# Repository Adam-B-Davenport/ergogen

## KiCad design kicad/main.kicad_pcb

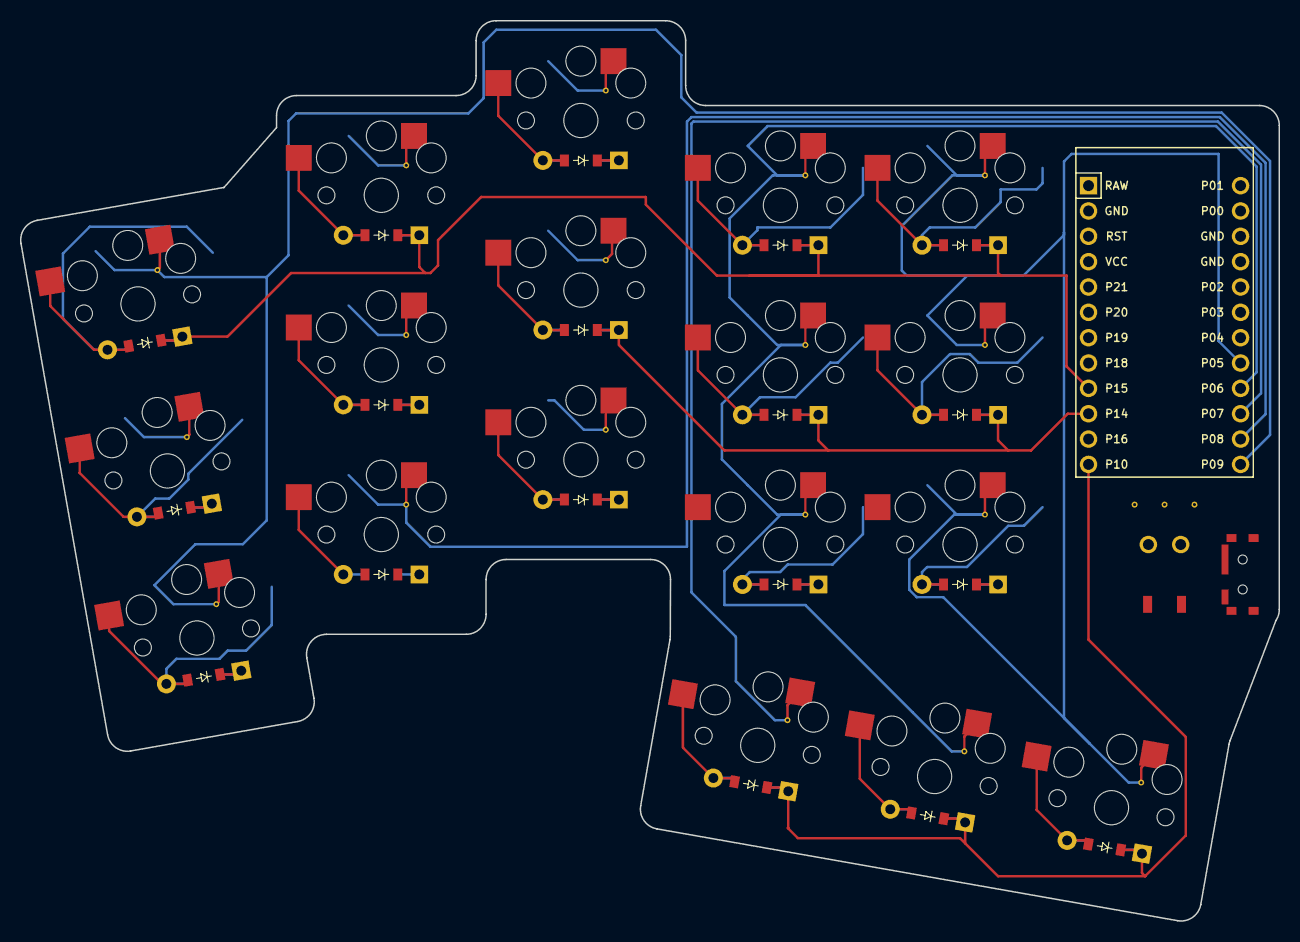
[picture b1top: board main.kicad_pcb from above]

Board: 2 copper layers, 126.1 x 90.2 mm, 37 parts (0 on the bottom side), 10 nets.

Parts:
D1, D2, D3, D4, D5, D6, D7, D8, D9, D10, D11, D12, D13, D14, D15, D16, D17, D18: ComboDiode
MCU1: ProMicro
S1, S2, S3, S4, S5, S6, S7, S8, S9, S10, S11, S12, S13, S14, S15, S16, S17, S18: PG1350

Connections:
GND: MCU1.2, MCU1.15, MCU1.16
P5: MCU1.20, S13.1, S14.1, S15.1, S18.1
P6: MCU1.21, S10.1, S11.1, S12.1, S17.1
P7: MCU1.22, S7.1, S8.1, S9.1, S16.1
P8: MCU1.23, S4.1, S5.1, S6.1
P9: MCU1.24, S1.1, S2.1, S3.1
P10: D16.1, D16.2, D17.1, D17.2, D18.1, D18.2, MCU1.12, S16.2, S17.2, S18.2
P14: D2.1, D2.2, D5.1, D5.2, D8.1, D8.2, D11.1, D11.2, D14.1, D14.2, MCU1.10, S2.2, S5.2, S8.2, S11.2, S14.2
P15: D3.1, D3.2, D6.1, D6.2, D9.1, D9.2, D12.1, D12.2, D15.1, D15.2, MCU1.9, S3.2, S6.2, S9.2, S12.2, S15.2
P16: D1.1, D1.2, D4.1, D4.2, D7.1, D7.2, D10.1, D10.2, D13.1, D13.2, MCU1.11, S1.2, S4.2, S7.2, S10.2, S13.2

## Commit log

2022-04-11 MK 3
2022-04-12 Adding components
2022-04-12 Fixing nets
2022-04-12 Shape
2022-04-12 Adding kicad files
2022-04-12 yml that was used in pcb
